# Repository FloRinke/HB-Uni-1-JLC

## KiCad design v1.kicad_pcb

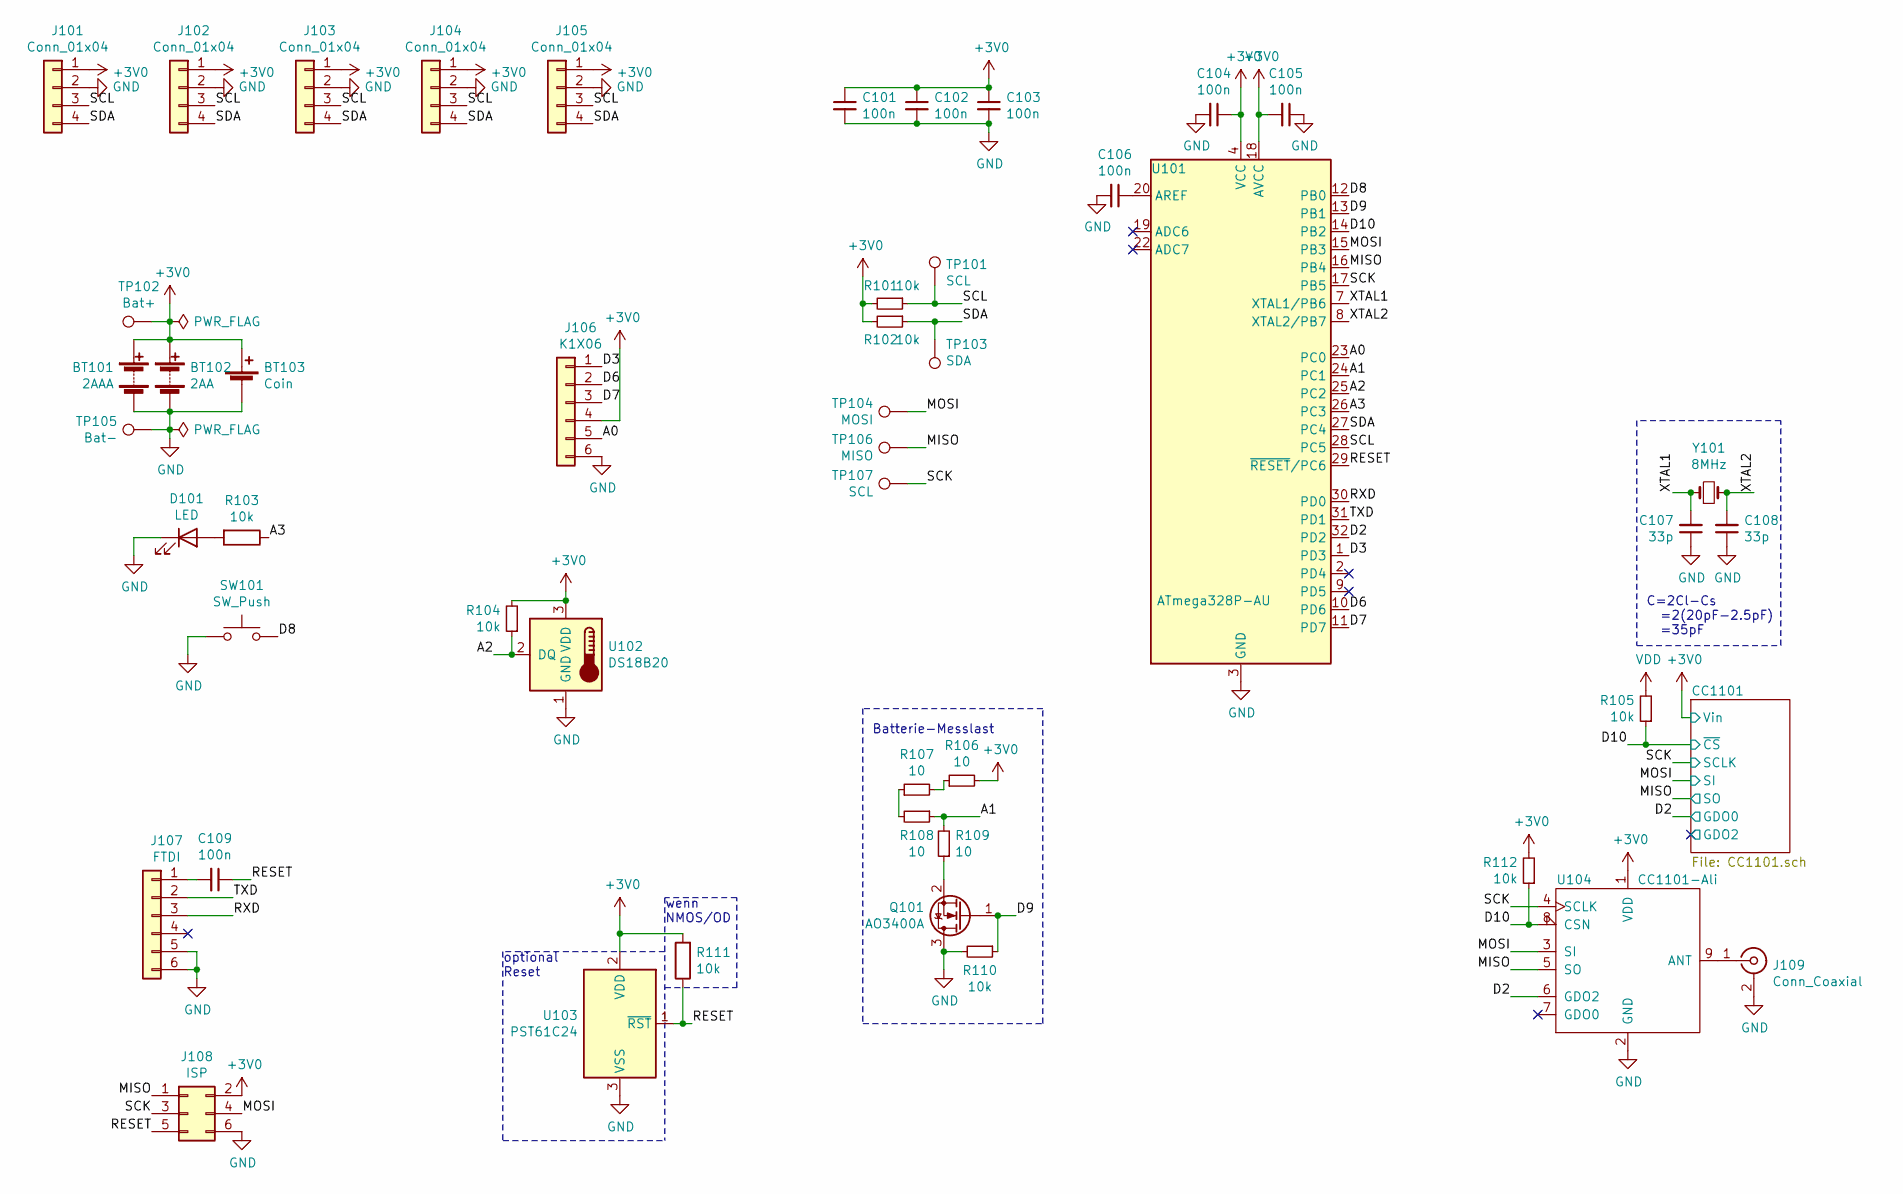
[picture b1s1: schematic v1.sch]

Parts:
BT101: 2AAA; BatteryHolder_Keystone_2468_2xAAA; JLCPCB BOM 0
BT102: 2AA; BatteryHolder_Keystone_2462_2xAA; JLCPCB BOM 0
BT103: Coin; BatteryHolder_Keystone_3000_1x12mm; JLCPCB BOM 0
C101, C102, C103, C104, C105, C106, C109: 100n; C_0402_1005Metric; LCSC C1525
C107, C108: 33p; C_0402_1005Metric; LCSC C1562
D101: LED; LED_0603_1608Metric; LCSC C72038
J101, J102, J103, J104, J105: Conn_01x04; PinSocket_1x04_P2.54mm_Vertical; JLCPCB BOM 0
J106: K1X06; PinSocket_1x06_P2.54mm_Vertical; JLCPCB BOM 0
J107: FTDI; PinSocket_1x06_P2.54mm_Vertical; JLCPCB BOM 0
J108: ISP; PinSocket_2x03_P2.54mm_Vertical; JLCPCB BOM 0
J109: Conn_Coaxial; SMA_Amphenol_901-144_Vertical
Q101: AO3400A; SOT-23; LCSC C20917
R101, R102, R103, R104, R105, R110, R112: 10k; R_0402_1005Metric; LCSC C25804
R106, R107, R108, R109: 10; R_0603_1608Metric; LCSC C22859
R111: 10k; R_0402_1005Metric; JLCPCB BOM 0
SW101: SW_Push; SW_SPST_CK_RS282G05A3; JLCPCB BOM 0
TP101, TP107: SCL; TestPoint_Keystone_5015_Micro-Minature; JLCPCB BOM 0
TP102: Bat+; TestPoint_Keystone_5015_Micro-Minature; JLCPCB BOM 0
TP103: SDA; TestPoint_Keystone_5015_Micro-Minature; JLCPCB BOM 0
TP104: MOSI; TestPoint_Keystone_5015_Micro-Minature; JLCPCB BOM 0
TP105: Bat-; TestPoint_Keystone_5015_Micro-Minature; JLCPCB BOM 0
TP106: MISO; TestPoint_Keystone_5015_Micro-Minature; JLCPCB BOM 0
U101: ATmega328P-AU; TQFP-32_7x7mm_P0.8mm; LCSC C14877
U102: DS18B20; TO-92_Inline; JLCPCB BOM 0
U103: PST61C24; SOT-23; LCSC C516359
U104: CC1101-Ali
Y101: 8MHz; Crystal_SMD_5032-2Pin_5.0x3.2mm; LCSC C115962

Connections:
+3V0: BT101.1 (+), BT102.1 (+), BT103.1 (+), C101.1, C102.1, C103.1, C104.1, C105.2, J101.1, J102.1, J103.1, J104.1, J105.1, J106.4, J108.2, R101.2, R102.2, R104.2, R106.2, R111.2, R112.2, TP102.1, U101.4 (VCC), U101.6 (VCC), U101.18 (AVCC), U102.3 (VDD), U103.2 (VDD), U104.1 (VDD); also elsewhere on the board
/A0: J106.5, U101.23 (PC0)
/A1: R108.1, R109.2, U101.24 (PC1)
/A2: R104.1, U101.25 (PC2), U102.2 (DQ)
/A3: R103.1, U101.26 (PC3)
/D2: U101.32 (PD2), U104.6 (GDO2); also elsewhere on the board
/D3: J106.1, U101.1 (PD3)
/D6: J106.2, U101.10 (PD6)
/D7: J106.3, U101.11 (PD7)
/D8: SW101.2, U101.12 (PB0)
/D9: Q101.1 (G), R110.1, U101.13 (PB1)
/D10: R105.1, R112.1, U101.14 (PB2), U104.8 (CSN); also elsewhere on the board
/MISO: J108.1, TP106.1, U101.16 (PB4), U104.5 (SO); also elsewhere on the board
/MOSI: J108.4, TP104.1, U101.15 (PB3), U104.3 (SI); also elsewhere on the board
/RESET: C109.1, J108.5, R111.1, U101.29 (~RESET~/PC6), U103.1 (~RST)
/RXD: J107.3, U101.30 (PD0)
/SCK: J108.3, TP107.1, U101.17 (PB5), U104.4 (SCLK); also elsewhere on the board
/SCL: J101.3, J102.3, J103.3, J104.3, J105.3, R101.1, TP101.1, U101.28 (PC5)
/SDA: J101.4, J102.4, J103.4, J104.4, J105.4, R102.1, TP103.1, U101.27 (PC4)
/TXD: J107.2, U101.31 (PD1)
/XTAL1: C107.2, U101.7 (XTAL1/PB6), Y101.1
/XTAL2: C108.2, U101.8 (XTAL2/PB7), Y101.2
GND: BT101.2 (-), BT102.2 (-), BT103.2 (-), C101.2, C102.2, C103.2, C104.2, C105.1, C106.2, C107.1, C108.1, D101.1 (K), J101.2, J102.2, J103.2, J104.2, J105.2, J106.6, J107.5, J107.6, J108.6, J109.2 (Ext), Q101.3 (D), R110.2, SW101.1, TP105.1, U101.3 (GND), U101.5 (GND), U101.21 (GND), U102.1 (GND), U103.3 (VSS), U104.2 (GND); also elsewhere on the board
unnamed: C106.1, U101.20 (AREF)
unnamed: C109.2, J107.1
unnamed: D101.2 (A), R103.2
unnamed: J109.1 (In), U104.9 (ANT)
unnamed: Q101.2 (S), R109.1
unnamed: R106.1, R107.2
unnamed: R107.1, R108.2
VDD: R105.2; also elsewhere on the board

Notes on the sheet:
Batterie-Messlast
optional Reset
C=2Cl-Cs =2(20pF-2.5pF) =35pF
wenn NMOS/OD

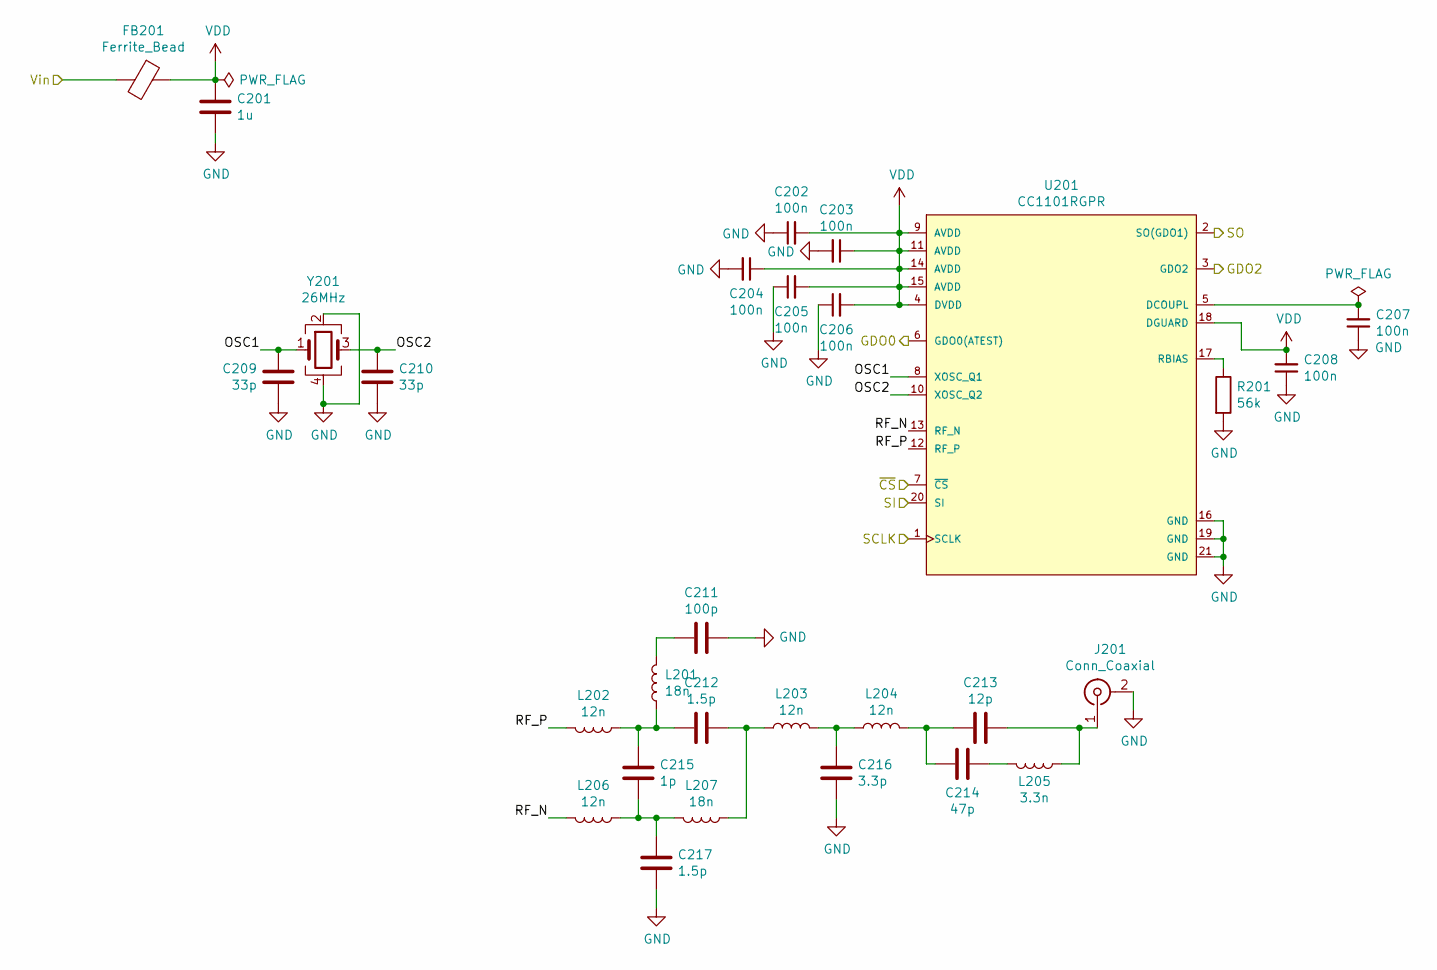
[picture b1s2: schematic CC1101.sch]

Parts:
C201: 1u; C_0805_2012Metric; LCSC C28323
C202, C203, C204, C205, C206, C207, C208: 100n; C_0402_1005Metric; LCSC C1525
C209, C210: 33p; C_0402_1005Metric; LCSC C1562
C211: 100p; C_0402_1005Metric; LCSC C1546
C212, C217: 1.5p; C_0402_1005Metric; LCSC C1552
C213: 12p; C_0402_1005Metric; LCSC C1547
C214: 47p; C_0402_1005Metric; LCSC C1567
C215: 1p; C_0402_1005Metric; LCSC C1550
C216: 3.3p; C_0402_1005Metric; LCSC C1565
FB201: Ferrite_Bead; L_0805_2012Metric; LCSC C1017
J201: Conn_Coaxial; SMA_Amphenol_901-144_Vertical; JLCPCB BOM 0
L201, L207: 18n; L_0402_1005Metric; LCSC C24562
L202, L203, L204, L206: 12n; L_0402_1005Metric; LCSC C24563
L205: 3.3n; L_0402_1005Metric
R201: 56k; R_0603_1608Metric; LCSC C23206
U201: CC1101RGPR; Texas_Instruments-RGP0020C-0-0-0; mouser part number 595-CC1101RGPR; LCSC C29953
Y201: 26MHz; Crystal_SMD_3225-4Pin_3.2x2.5mm; LCSC C258950

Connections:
+3V0: FB201.2; also elsewhere on the board
/CC1101/OSC1: C209.1, U201.8 (XOSC_Q1), Y201.1
/CC1101/OSC2: C210.1, U201.10 (XOSC_Q2), Y201.3
/CC1101/RF_N: L206.2, U201.13 (RF_N)
/CC1101/RF_P: L202.2, U201.12 (RF_P)
/D2: U201.6 (GDO0(ATEST)); also elsewhere on the board
/D10: U201.7 (~CS~); also elsewhere on the board
/MISO: U201.2 (SO(GDO1)); also elsewhere on the board
/MOSI: U201.20 (SI); also elsewhere on the board
/SCK: U201.1 (SCLK); also elsewhere on the board
GND: C201.2, C202.1, C203.2, C204.2, C205.1, C206.1, C207.1, C208.1, C209.2, C210.2, C211.1, C216.2, C217.2, J201.2 (Ext), R201.2, U201.16 (GND), U201.19 (GND), U201.21 (GND), Y201.2, Y201.4; also elsewhere on the board
unnamed: C207.2, U201.5 (DCOUPL)
unnamed: C211.2, L201.2
unnamed: C212.1, L203.1, L207.1
unnamed: C212.2, C215.1, L201.1, L202.1
unnamed: C213.1, J201.1 (In), L205.1
unnamed: C213.2, C214.2, L204.2
unnamed: C214.1, L205.2
unnamed: C215.2, C217.1, L206.1, L207.2
unnamed: C216.1, L203.2, L204.1
unnamed: R201.1, U201.17 (RBIAS)
VDD: C201.1, C202.2, C203.1, C204.1, C205.2, C206.2, C208.2, FB201.1, U201.4 (DVDD), U201.9 (AVDD), U201.11 (AVDD), U201.14 (AVDD), U201.15 (AVDD), U201.18 (DGUARD); also elsewhere on the board

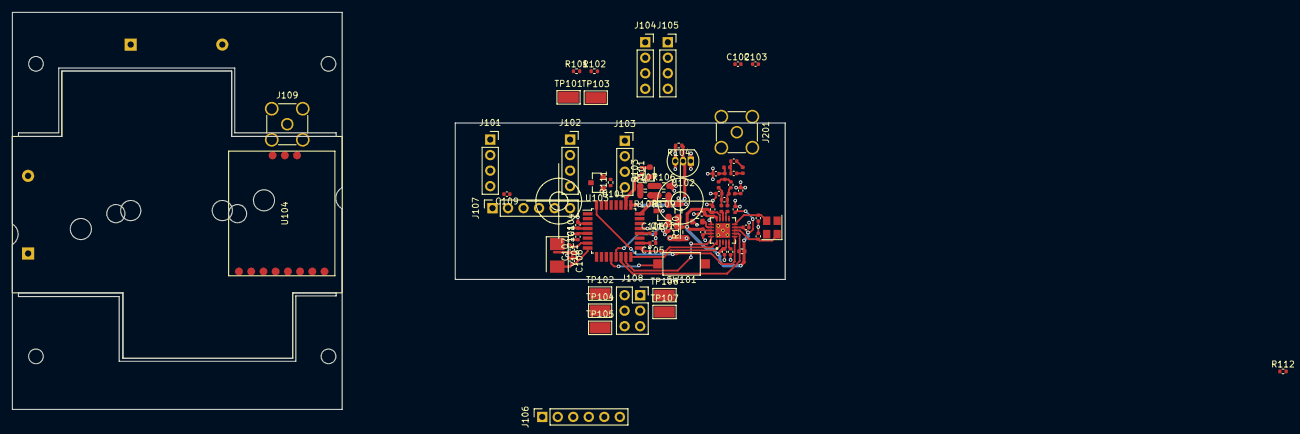
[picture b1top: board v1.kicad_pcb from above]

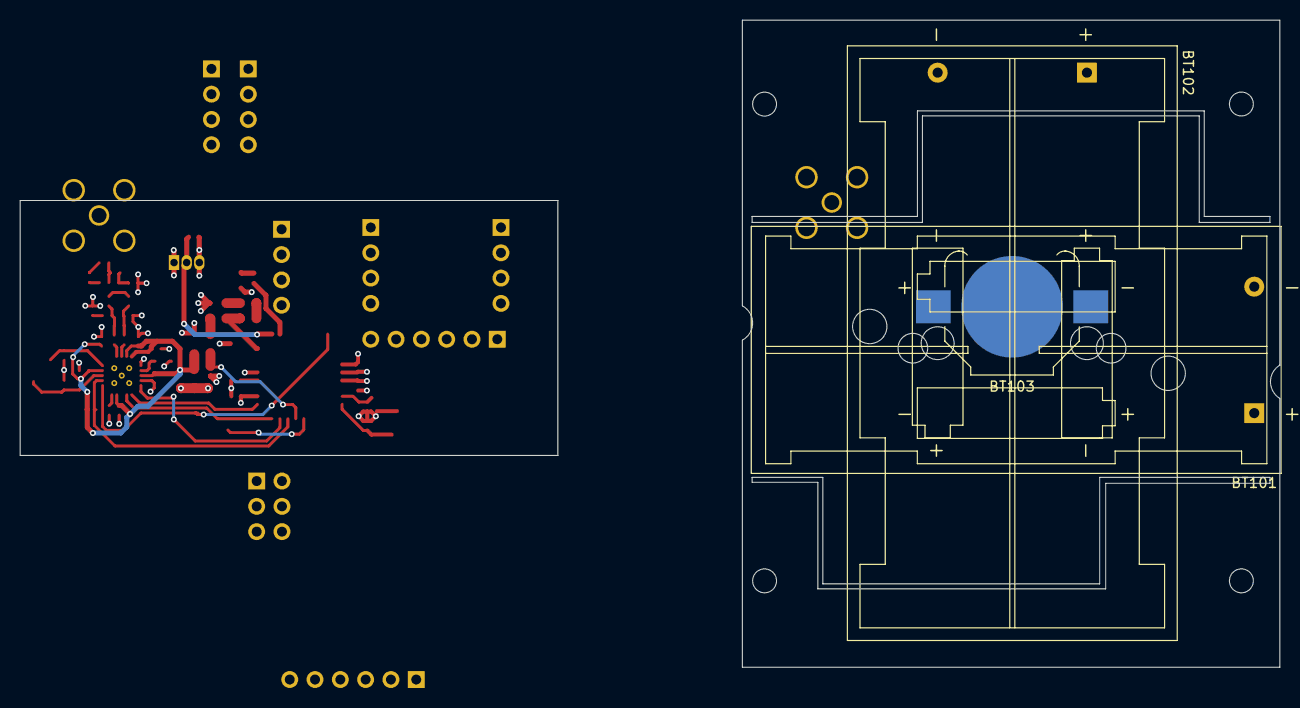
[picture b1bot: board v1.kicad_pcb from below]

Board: 2 copper layers, 126.5 x 65.0 mm, 77 parts (3 on the bottom side), 45 nets.

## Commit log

2021-04-25 add gitignore for kicad
2021-04-25 select more JLC components
2021-04-25 add first draft
2021-04-25 raw component placement
2021-04-25 place CC1101 circuits
2021-04-25 place Atmega328 circuits
2021-05-03 add cc1101 module as footprint
2021-05-03 adapt boards for kradex casings
